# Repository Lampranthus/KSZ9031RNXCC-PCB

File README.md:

# Spartan-6 1GbE Interface

A **1 Gbps Ethernet UDP communication system** implemented on a Xilinx Spartan-6 FPGA with a KSZ9031 Gigabit PHY. Achieves ~1 Gbps throughput in TX, RX, and full-duplex modes, controlled via UART or UDP commands.

## Hardware

| Component | Part |
|-----------|------|
| FPGA | Xilinx Spartan-6 XC6SLX9-2TQG144C |
| PHY | KSZ9031RNXCC |
| Connector | ARJM11B1-502-AB-EW2 |

---

## Features

- **UDP TX/RX** at line rate (~1 Gbps)
- **Full-duplex** simultaneous TX + RX (237 MB/s measured)
- **UART control interface** — configure and trigger tests via serial commands
- **UDP command interface** — remotely set packet count, size, and rate
- **ARP support** — FPGA responds to ARP requests
- **Software shutdown mode** — low-power state via command (~159 mA)

---

## Board Controls

### Switches & LEDs

| Switch | Function | LED | Indicates |
|--------|----------|-----|-----------|
| SW[0] | Indicator state | LED[0] | Global reset_n |
| SW[1] | Indicator state | LED[1] | UART/MDIO reset_n |
| SW[2] | Indicator state | LED[2] | PHY PLL 125 MHz_n |
| SW[3] | Indicator state | LED[3] | PHY interrupt |
| SW[4] | Indicator state | LED[4] | UDP loopback mode |
| SW[5] | Indicator state | LED[5] | UDP random or constant data mode |
| SW[6] | Indicator state | LED[6] | UDP transmitting |
| SW[7] | Indicator state | LED[7] | MDIO busy |

### Push Buttons

| Button | Function |
|--------|----------|
| PUSH[0] | PHY reset |
| PUSH[1] | Reset UART and MDIO interfaces |
| PUSH[2] | Global reset |

---

## UDP Operation Modes

| Mode | Description |
|------|-------------|
| Default | Generate and transmit sequence data |
| Loopback | Echo received packets back to sender |
| Random data | Generate and transmit random data |
| Constant data | Transmit predefined data "X" or h58 |

---

## UART Command Interface

### Serial Configuration

| Parameter | Value |
|-----------|-------|
| Baud rate | 115200 |
| Data bits | 8 |
| Stop bits | 1 |
| Parity | None |

### Sending Commands

Commands are sent using `send_uart.py`. Multiple commands can be chained in a single call — they are concatenated in order with no separator:

```bash
python3 send_uart.py command1 command2 command3
```

> **Hardware constraint:** every transmission must be exactly **8 bytes or a multiple of 8 bytes**. The script enforces this and will error before touching the serial port if the length is wrong.

---

### UDP Control Commands
| Command | Hex | Description |
|---------|-----|-------------|
| `loopback` | `6C6F6F706261636B` | Enable loopback mode (LED[4] on) |
| `.trigger` | `2E74726967676572` | Send a trigger pulse |
| `..random` | `2E2E72616E646F6D` | Enable random data mode (LED[5] on) |
| `...flood` | `2E2E2E666C6F6F64` | Transmit as fast as possible |
| `udpmtu\xHH\xHH` | `7564706D7475HHHH` | Set MTU size (16-bit, default `\x05\xA0` = 1440 B) |
| `pktn\xHH\xHH\x00\x00` | `706B746EHHHHHHHH` | Set packet count per trigger (32-bit, default `\x00\x00\x00\x01` = 1) |

---

### IP / Network Configuration Commands
| Command | Hex | Description |
|---------|-----|-------------|
| `ip_g\xII\xII\xII\xII` | `69705F67IIIIIIII` | Set gateway IP (32-bit) |
| `ip_s\xII\xII\xII\xII` | `69705F73IIIIIIII` | Set local/source IP (32-bit) |
| `ip_d\xII\xII\xII\xII` | `69705F64IIIIIIII` | Set destination IP (32-bit) |
| `subm\xMM\xMM\xMM\xMM` | `7375626DMMMMMMM` | Set subnet mask (32-bit) |
| `srport\xPP\xPP` | `7372706F7274PPPP` | Set UDP source port (16-bit) |
| `dsport\xPP\xPP` | `6473706F7274PPPP` | Set UDP destination port (16-bit) |

> **IP format:** IPs are sent as raw 32-bit big-endian values.
> Example: `192.168.1.100` → `\xC0\xA8\x01\x64`

---

### MDIO / PHY Control Commands
| Command | Hex | Description |
|---------|-----|-------------|
| `..mdio_w` | `2E2E6D64696F5F77` | Switch to MDIO write mode |
| `..mdio_r` | `2E2E6D64696F5F72` | Switch to MDIO read mode (default) |
| `phyaddr\xHH` | `70687961646472HH` | Set PHY address (5 LSBs of `\xHH`, default `\x07`) |
| `regaddr\xHH` | `72656761646472HH` | Set register address (5 LSBs of `\xHH`, default `\x00`) |
| `mdio_d\xHH\xHH` | `6D64696F5F64HHHH` | Set 16-bit write data |
| `mdio_sta` | `6D64696F5F737461` | Start MDIO operation |

### MDIO Transaction Sequence

```
1. Set mode      →  ..mdio_r  or  ..mdio_w
2. Set PHY addr  →  phyaddr\xHH
3. Set reg addr  →  regaddr\xHH
4. Set data      →  mdio_d\xHH\xHH   (write operations only)
5. Execute       →  mdio_sta
```

Always return to read mode after a write to leave the interface in a safe state.

---

## Command Examples

### Read PHY register (default config)

```bash
python3 send_uart.py ..mdio_r "phyaddr\x07" "regaddr\x00" mdio_sta
```

Sequence: read mode → PHY 7 → register 0 → execute

---

### Write to PHY register, then read back to confirm

```bash
python3 send_uart.py ..mdio_w "phyaddr\x07" "regaddr\x00" "mdio_d\x11\x40" mdio_sta ..mdio_r mdio_sta
```

| Step | Command | Action |
|------|---------|--------|
| 1 | `..mdio_w` | Switch to write mode |
| 2 | `phyaddr\x07` | Target PHY 7 |
| 3 | `regaddr\x00` | Target register 0 |
| 4 | `mdio_d\x11\x40` | Write data = 0x1140 |
| 5 | `mdio_sta` | Execute write |
| 6 | `..mdio_r` | Switch back to read mode |
| 7 | `mdio_sta` | Execute read (verify) |

---

### Common MDIO sequences

| Purpose | Command |
|---------|---------|
| Read PHY 7, reg 0 | `python3 send_uart.py ..mdio_r "phyaddr\x07" "regaddr\x00" mdio_sta` |
| Write default config (PHY 7, reg 0) | `python3 send_uart.py ..mdio_w "phyaddr\x07" "regaddr\x00" "mdio_d\x11\x40" mdio_sta ..mdio_r mdio_sta` |
| Software reset (PHY 7) | `python3 send_uart.py ..mdio_w "phyaddr\x07" "regaddr\x00" "mdio_d\x91\x40" mdio_sta ..mdio_r mdio_sta` |
| Power down (PHY 7) | `python3 send_uart.py ..mdio_w "phyaddr\x07" "regaddr\x00" "mdio_d\x19\x40" mdio_sta ..mdio_r mdio_sta` |

---

### MDIO MMD Register Access

MMD (MIIM Managed Device) registers are accessed indirectly using the **MDIO address registers D (0x0D) and E (0x0E)**.

The access sequence is always:
1. Write the MMD device address to register `0x0D`
2. Write the target register address to register `0x0E`
3. Write the function (read/write + optional auto-increment) back to `0x0D`
4. Read or write data via register `0x0E`

#### Write MMD — Example: MMD device `0x02`, register `0x00` ← `0x0010`

```bash
# Step 1 — Select MMD device address (device = 0x02)
python3 send_uart.py ..mdio_w "phyaddr\x07" "regaddr\x0D" "mdio_d\x00\x02" mdio_sta

# Step 2 — Select target register inside the MMD (register = 0x0000)
python3 send_uart.py ..mdio_w "phyaddr\x07" "regaddr\x0E" "mdio_d\x00\x00" mdio_sta

# Step 3 — Switch to data function, no auto-increment (0x4000 | device)
python3 send_uart.py ..mdio_w "phyaddr\x07" "regaddr\x0D" "mdio_d\x40\x02" mdio_sta

# Step 4 — Write new data to the MMD register
python3 send_uart.py ..mdio_w "phyaddr\x07" "regaddr\x0E" "mdio_d\x00\x10" mdio_sta
```

> **`0x4002`** = data function (bits [15:14] = `01`) + device `0x02`, no auto-increment.
> **`0x8002`** = data function with post-increment (bits [15:14] = `10`) + device `0x02`.

---

#### Read MMD — Example: MMD device `0x02`, registers `0x00` → `0x02` (burst with auto-increment)

```bash
# Step 1 — Select MMD device address (device = 0x02)
python3 send_uart.py ..mdio_w "phyaddr\x07" "regaddr\x0D" "mdio_d\x00\x02" mdio_sta

# Step 2 — Select starting register (register = 0x0000)
python3 send_uart.py ..mdio_w "phyaddr\x07" "regaddr\x0E" "mdio_d\x00\x00" mdio_sta

# Step 3 — Switch to data function WITH auto-increment (0x8000 | device)
python3 send_uart.py ..mdio_w "phyaddr\x07" "regaddr\x0D" "mdio_d\x80\x02" mdio_sta

# Step 4 — Read register 0x00
python3 send_uart.py ..mdio_r "phyaddr\x07" "regaddr\x0E" mdio_sta

# Step 5 — Read register 0x01 (auto-incremented)
python3 send_uart.py ..mdio_r "phyaddr\x07" "regaddr\x0E" mdio_sta

# Step 6 — Read register 0x02 (auto-incremented)
python3 send_uart.py ..mdio_r "phyaddr\x07" "regaddr\x0E" mdio_sta
```

---

#### One-liner shortcuts

```bash
# Full write — MMD 0x02, reg 0x00 ← 0x0008
python3 send_uart.py ..mdio_w \
  "phyaddr\x07" "regaddr\x0D" "mdio_d\x00\x02" mdio_sta \
  "regaddr\x0E" "mdio_d\x00\x00"               mdio_sta \
  "regaddr\x0D" "mdio_d\x40\x02"               mdio_sta \
  "regaddr\x0E" "mdio_d\x00\x08"               mdio_sta

# Full read — MMD 0x02, reg 0x00 (single, no auto-increment)
python3 send_uart.py ..mdio_w \
  "phyaddr\x07" "regaddr\x0D" "mdio_d\x00\x02" mdio_sta \
  "regaddr\x0E" "mdio_d\x00\x00"               mdio_sta \
  "regaddr\x0D" "mdio_d\x40\x02"               mdio_sta \
  ..mdio_r "regaddr\x0E" mdio_sta
```

#### Register `0x0D` function field reference

| Bits [15:14] | Value | Function |
|---|---|---|
| `00` | `0x0000` \| device | Address function — points to MMD register |
| `01` | `0x4000` \| device | Data function — no auto-increment |
| `10` | `0x8000` \| device | Data function — post-increment on each access read or write |
| `11` | `0xC000` \| device | Data function — post increment on writes only |

---

## Network Setup

Set up a `192.168.1.1/24` network between your PC and the FPGA:

| Device | IP Address |
|--------|------------|
| FPGA (default) | `192.168.1.12` |
| PC (default) | `192.168.1.11` |

> IPv6 must be disabled on the interface for compatibility.

Configure the PC interface:

```bash
sudo ip addr flush dev eth0
sudo ip addr add 192.168.1.11/24 dev eth0
sudo ip link set eth0 up
```

Verify ARP (confirms the FPGA link is up):

```bash
sudo arping -I eth0 -c 10 192.168.1.12
```

---

## Throughput Tests

### TX Test (~1 Gbps)

Terminal 1 — monitor traffic:
```bash
sudo tcpdump -i eth0 udp -w - | pv > /dev/null
```

Terminal 2 — trigger transmission (set ~1 M packets first for accurate results):
```bash
python3 send_uart.py .trigger
```

> Expected: **~118 MB/s ≈ 0.994 Gbps**

---

### RX Test

Terminal 1 — flood UDP packets to the FPGA:
```bash
sudo hping3 192.168.1.12 -2 -p 1234 -d 1440 --flood
```

Terminal 2 — monitor received traffic:
```bash
sudo tcpdump -i eth0 udp -w - | pv > /dev/null
```

---

### Full-Duplex Test (TX + RX simultaneously)

Run both the TX and RX tests at the same time and monitor with:
```bash
sudo tcpdump -i eth0 udp -w - | pv > /dev/null
```

> **Measured: 237 MB/s (~1 Gbps full-duplex confirmed)**
> ```
> tcpdump: listening on eth0, link-type EN10MB (Ethernet), snapshot length 262144 bytes
> 26.9GiB 0:03:54 [236MiB/s]
> ```

---

## Power Consumption

Measurements include FPGA + PHY at 1 Gbps link speed.

| Mode | Current |
|------|---------|
| Standby (1 Gbps link up) | ~467 mA |
| Software shutdown | ~159 mA |
| Full duplex (1 Gbps) | ~552 mA |

---

## Troubleshooting

| Symptom | Solution |
|---------|---------|
| No response from FPGA | Check USB connection and power supply |
| LEDs all off | Verify switch positions (SW[1] enables LEDs) |
| LED[7] stuck on | MDIO busy — wait for operation to complete before sending next command |
| Unexpected data received | Verify baud rate is set to 115200 |
| Script errors before sending | Payload length must be a multiple of 8 bytes — add `\x00` padding |

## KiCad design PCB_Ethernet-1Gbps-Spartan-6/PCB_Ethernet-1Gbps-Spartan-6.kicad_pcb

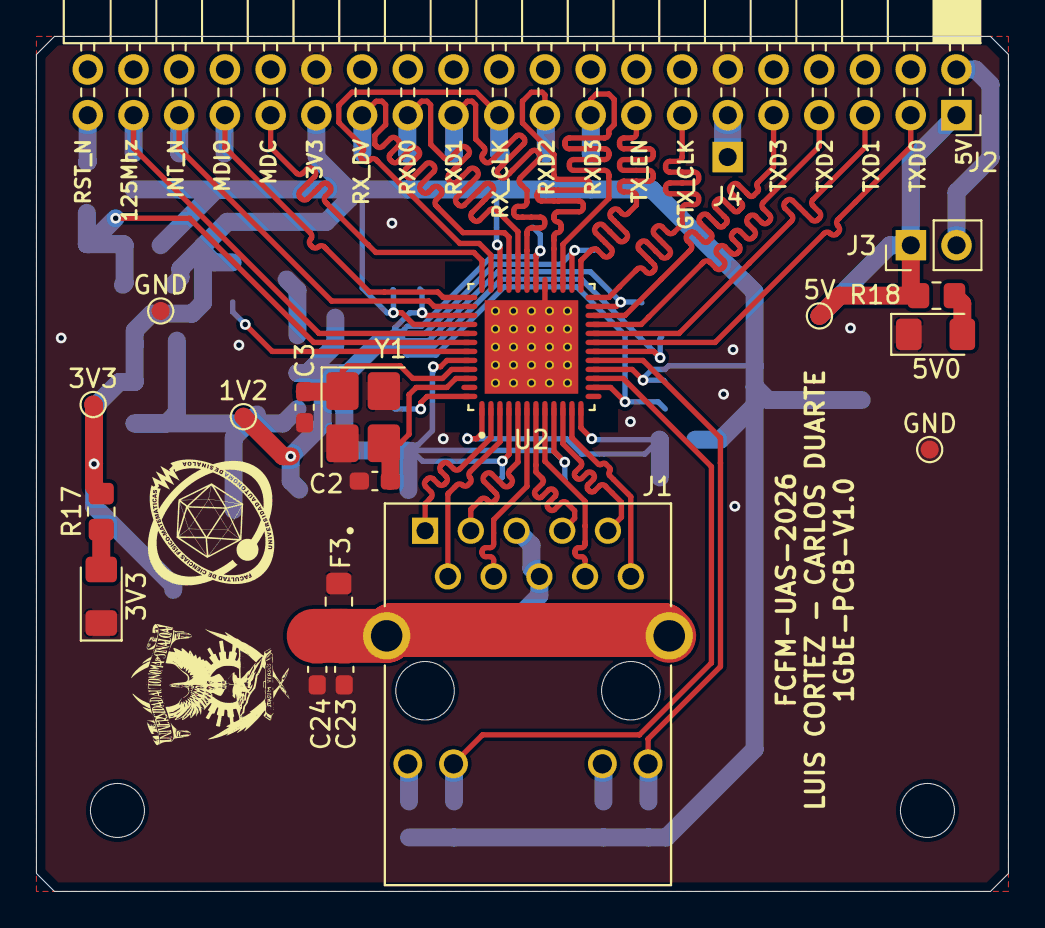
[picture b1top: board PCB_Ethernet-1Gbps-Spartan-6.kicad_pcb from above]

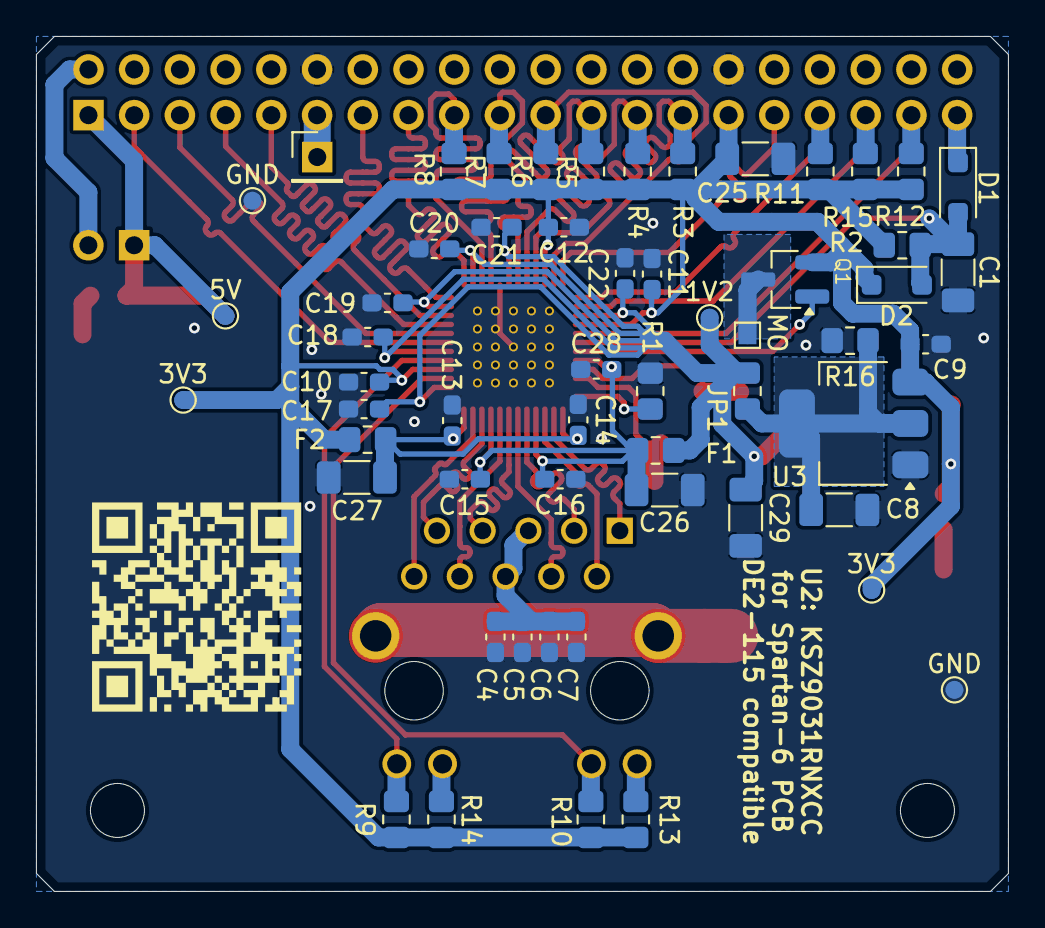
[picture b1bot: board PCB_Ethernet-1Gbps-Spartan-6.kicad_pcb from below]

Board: 2 copper layers, 54.0 x 47.5 mm, 75 parts (56 on the bottom side), 48 nets.

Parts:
1V2, 1V2#2, 3V3#2, 3V3#3, 3V3#4, 5V, 5V#2: TestPoint_Pad_D1.0mm
3V3, 5V0: LED; LED_1206_3216Metric_Pad1.42x1.75mm_HandSolder
C1, C8, C25, C26, C27, C29: 10uF; C_1206_3216Metric_Pad1.33x1.80mm_HandSolder
C2, C3: 22pF; C_0603_1608Metric_Pad1.08x0.95mm_HandSolder
C4, C5, C6, C7, C9, C10, C11, C12, C13, C14, C15, C16, C17, C18, C19, C20, C21, C22, C23, C24, C28: 0.1uF; C_0603_1608Metric_Pad1.08x0.95mm_HandSolder
D1, D2: 1N4148; D_SOD-123F
F1, F2, F3: 0; R_0805_2012Metric_Pad1.20x1.40mm_HandSolder
GND: TestPoint_Pad_D1.0mm
GND#2, GND#3, GND#4: TestPoint_Pad_D1.0mm
J1: ARJM11B1-502-AB-EW2; ABRACON_ARJM11B1-502-AB-EW2
J2: Conn_02x20_Odd_Even; PinSocket_2x20_P2.54mm_Horizontal
J3: Conn_01x02_Pin; PinHeader_1x02_P2.54mm_Vertical
J4: Conn_01x01_Pin; PinHeader_1x01_P2.54mm_Vertical
JP1: 0; R_0805_2012Metric_Pad1.20x1.40mm_HandSolder
MO: TestPoint_Pad_1.0x1.0mm
Q1: PMOS; SOT-23_Handsoldering
R1: 12.1k; R_0805_2012Metric_Pad1.20x1.40mm_HandSolder
R2, R3, R4, R5, R6, R7, R8, R9, R10, R12: 10k; R_0805_2012Metric_Pad1.20x1.40mm_HandSolder
R11, R15: 1k; R_0805_2012Metric_Pad1.20x1.40mm_HandSolder
R13, R14, R17, R18: 220; R_0805_2012Metric_Pad1.20x1.40mm_HandSolder
R16: 120; R_0805_2012Metric_Pad1.20x1.40mm_HandSolder
U2: KSZ9031RNXCC; IC_KSZ9031RNXCC
U3: LD1117S12TR_SOT223; SOT-223-3_TabPin2
Y1: 25Mhz; Crystal_SMD_3225-4Pin_3.2x2.5mm_HandSoldering

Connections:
1.2V: 1V2.1, 1V2#2.1, C17.2, C18.2, C19.2, C20.2, C21.2, C22.2, C29.1, F1.2, JP1.1, U2.14 (DVDDL), U2.18 (DVDDL__1), U2.23 (DVDDL__2), U2.26 (DVDDL__3), U2.30 (DVDDL__4), U2.39 (DVDDL__5)
1V2_L: C8.1, JP1.2, R16.2, U3.2 (VO)
3.3V: 3V3#2.1, 3V3#3.1, 3V3#4.1, C9.2, C10.2, C11.2, C12.2, C25.1, D2.1 (K), F2.2, J2.29, Q1.3 (S), R2.2, R3.2, R4.2, R5.2, R6.2, R7.2, R8.2, R9.2, R10.2, R11.2, R12.2, R13.2, R14.2, R15.2, R17.2, U2.16 (DVDDH), U2.34 (DVDDH__1), U2.40 (DVDDH__2), U3.3 (VI)
5V: 5V.1, 5V#2.1, J2.1, J3.1, R18.2
125Mhz: J2.37, R12.1, U2.41 (CLK125_NDO/LED_MODE)
A1.2V: C15.2, C16.2, C26.1, C28.2, F1.1, U2.4 (AVDDL), U2.9 (AVDDL__1), U2.44 (AVDDL_PLL)
A3.3V: C13.2, C14.2, C27.1, F2.1, U2.1 (AVDDH), U2.12 (AVDDH__1)
AGND: C23.2, C24.2, F3.2, J1.S1 (SHIELD), J1.S2 (SHIELD__1)
CT: C4.2, C5.2, C6.2, C7.2, J1.5 (CT), J1.6 (CT__1)
GND: 3V3.1 (K), 5V0.1 (K), C1.2, C2.2, C3.2, C4.1, C5.1, C6.1, C7.1, C8.2, C9.1, C10.1, C11.1, C12.1, C13.1, C14.1, C15.1, C16.1, C17.1, C18.1, C19.1, C20.1, C21.1, C22.1, C23.1, C24.1, C25.2, C26.2, C27.2, C28.1, C29.2, F3.1, GND.1, GND#2.1, GND#3.1, GND#4.1, J2.12, J2.30, R1.1, R16.1, U2.29 (VSS), U2.49 (P_GND), U2.49_1 (P_GND__1), U2.49_2 (P_GND__2), U2.49_3 (P_GND__3), U2.49_4 (P_GND__4), U2.49_5 (P_GND__5), U2.49_6 (P_GND__6), U2.49_7 (P_GND__7), U2.49_8 (P_GND__8), U2.49_9 (P_GND__9), U2.49_10 (P_GND__10), U2.49_11 (P_GND__11), U2.49_12 (P_GND__12), U2.49_13 (P_GND__13), U2.49_14 (P_GND__14), U2.49_15 (P_GND__15), U2.49_16 (P_GND__16), U2.49_17 (P_GND__17), U2.49_18 (P_GND__18), U2.49_19 (P_GND__19), U2.49_20 (P_GND__20), U2.49_21 (P_GND__21), U2.49_22 (P_GND__22), U2.49_23 (P_GND__23), U2.49_24 (P_GND__24), U2.49_25 (P_GND__25), U3.1 (GND), Y1.2, Y1.4
GTX_CLK: J2.13, U2.24 (GTX_CLK)
INT_N: J2.35, R15.1, U2.38 (INT_N/PME_N2)
LDO_1V2: MO.1, Q1.1 (D)
LDO_O: Q1.2 (G), U2.43 (LDO_O)
LED1: J1.14, R9.1, U2.17 (LED1/PHYAD0/PME_N1)
LED2: J1.12, R10.1, U2.15 (LED2/PHYAD1)
MDC: J2.31, U2.36 (MDC)
MDIO: J2.33, R11.1, U2.37 (MDIO)
unnamed: 3V3.2 (A), R17.1
unnamed: 5V0.2 (A), R18.1
unnamed: C1.1, D1.2 (A), D2.2 (A), R2.1, U2.42 (~RESET_N)
unnamed: J1.11, R13.1
unnamed: J1.13, R14.1
unnamed: J2.2, J3.2
unnamed: J2.11, J4.1
unnamed: R1.2, U2.48 (ISET)
unnamed: C2.1, U2.46 (XI), Y1.3
unnamed: C3.1, U2.45 (XO), Y1.1
RST_N: D1.1 (K), J2.39
RXD0: J2.25, R5.1, U2.32 (RXD0/MODE0)
RXD1: J2.23, R6.1, U2.31 (RXD1/MODE1)
RXD2: J2.19, R7.1, U2.28 (RXD2/MODE2)
RXD3: J2.17, R8.1, U2.27 (RXD3/MODE3)
RX_CLK: J2.21, R3.1, U2.35 (RX_CLK/PHYAD2)
RX_DV: J2.27, R4.1, U2.33 (RX_DV/CLK125_EN)
TD1+: J1.1 (TD1+), U2.2 (TXRXP_A)
TD1-: J1.2 (TD1-), U2.3 (TXRXM_A)
TD2+: J1.3 (TD2+), U2.5 (TXRXP_B)
TD2-: J1.4 (TD2-), U2.6 (TXRXM_B)
TD3+: J1.7 (TD3+), U2.7 (TXRXP_C)
TD3-: J1.8 (TD3-), U2.8 (TXRXM_C)
TD4+: J1.9 (TD4+), U2.10 (TXRXP_D)
TD4-: J1.10 (TD4-), U2.11 (TXRXM_D)
TXD0: J2.3, U2.19 (TXD0)
TXD1: J2.5, U2.20 (TXD1)
TXD2: J2.7, U2.21 (TXD2)
TXD3: J2.9, U2.22 (TXD3)
TX_EN: J2.15, U2.25 (TX_EN)

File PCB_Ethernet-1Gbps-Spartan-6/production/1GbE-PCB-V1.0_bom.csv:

Designator,Footprint,Quantity,Value,LCSC Part #
"3V3_4, 5V1",1206,2,LED,
"C1, C25, C26, C27, C29, C8",1206,6,10uF,
"C10, C11, C12, C13, C14, C15, C16, C17, C18, C19, C20, C21, C22, C23, C24, C28, C4, C5, C6, C7, C9",0603,21,0.1uF,
"C2, C3",0603,2,22pF,
"D1, D2",D_SOD-123F,2,1N4148,
"F1, F2, F3, JP1",0805,4,0,
J1,ABRACON_ARJM11B1-502-AB-EW2,1,ARJM11B1-502-AB-EW2,
J2,PinSocket_2x20_P2.54mm_Horizontal,1,Conn_02x20_Odd_Even,
J3,PinHeader_1x02_P2.54mm_Vertical,1,Conn_01x02_Pin,
Q1,SOT-23_Handsoldering,1,PMOS,
R1,0805,1,12.1k,
"R10, R12, R2, R3, R4, R5, R6, R7, R8, R9",0805,10,10k,
"R11, R15",0805,2,1k,
"R13, R14, R17, R18",0805,4,220,
R16,0805,1,120,
U2,IC_KSZ9031RNXCC,1,KSZ9031RNXCC,
U3,SOT-223-3_TabPin2,1,LD1117S12TR_SOT223,
Y1,Crystal_SMD_3225-4Pin_3.2x2.5mm_HandSoldering,1,25Mhz,

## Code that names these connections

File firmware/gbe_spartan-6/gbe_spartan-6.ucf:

NET "*" IOSTANDARD=LVCMOS33;
CONFIG VCCAUX = "2.5" ;

// 50Mhz Clock
NET "clk" LOC = "P56";
NET "clk" TNM_NET = "sys_clk_pin";
TIMESPEC "TS_sys_clk_pin" = PERIOD "sys_clk_pin" 20.000ns HIGH 50%;

// Dip Switch
NET "sw<0>" LOC = "P35";
NET "sw<1>" LOC = "P34";
NET "sw<2>" LOC = "P33";
NET "sw<3>" LOC = "P32";
NET "sw<4>" LOC = "P30";
NET "sw<5>" LOC = "P29";
NET "sw<6>" LOC = "P27";
NET "sw<7>" LOC = "P26";

// Red LEDs
NET "led<0>" LOC = "P74";
NET "led<1>" LOC = "P75";
NET "led<2>" LOC = "P78";
NET "led<3>" LOC = "P79";
NET "led<4>" LOC = "P80";
NET "led<5>" LOC = "P81";
NET "led<6>" LOC = "P82";
NET "led<7>" LOC = "P83";

// Push buttons
NET "push<0>" LOC = "P144";
NET "push<1>" LOC = "P143";
NET "push<2>" LOC = "P142";

// UART
NET "txd" LOC = "P100";
NET "rxd" LOC = "P101";

// Molex
//NET "molex<0>" LOC = "P141";
//NET "molex<1>" LOC = "P140";

// Single
//NET "pin0" LOC = "P139";

// Pin Header 
NET "ENET0_TX_DATA<0>" LOC = "P138" | SLEW = SLOW | DRIVE = 4; // RGMMII TXD0
NET "ENET0_TX_DATA<1>" LOC = "P137" | SLEW = SLOW | DRIVE = 4; // RGMMII TXD1
NET "ENET0_TX_DATA<2>" LOC = "P134" | SLEW = SLOW | DRIVE = 4; // RGMMII TXD2
NET "ENET0_TX_DATA<3>" LOC = "P133" | SLEW = SLOW | DRIVE = 4; // RGMMII TXD3
//NET "NC0" LOC = "P132"; // No connection
NET "ENET0_GTX_CLK" LOC = "P131" | SLEW = SLOW | DRIVE = 4; // RGMMII GTX_CLK
NET "ENET0_TX_EN" LOC = "P127" | SLEW = SLOW | DRIVE = 4; // RGMMII TX_EN
NET "ENET0_RX_DATA<3>" LOC = "P126" | IOB = TRUE; // RGMMII RXD3
NET "ENET0_RX_DATA<2>" LOC = "P124" | IOB = TRUE; // RGMMII RXD2 
NET "ENET0_RX_CLK" LOC = "P123" | IOB = TRUE; // RGMMII RX_CLK 
NET "ENET0_RX_CLK" TNM_NET = "rx_clk_pin";
TIMESPEC "TS_rx_clk_pin" = PERIOD "rx_clk_pin" 8.000ns HIGH 50%;
NET "ENET0_RX_DATA<1>" LOC = "P121" | IOB = TRUE; // RGMMII RXD1 
NET "ENET0_RX_DATA<0>" LOC = "P120" | IOB = TRUE; // RGMMII RXD0 
NET "ENET0_RX_DV" LOC = "P119" | IOB = TRUE; // RGMMII RX_DV
NET "V3_3" LOC = "P118"; // 3.3V in when pcb energized
NET "MDC" LOC = "P117";
NET "MDIO" LOC = "P116";
NET "ENET0_INT_N" LOC = "P115";
NET "CLK_125MHZ" LOC = "P114";
NET "ENET0_RST_N" LOC = "P112";  // RGMMII RST_N

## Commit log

2026-02-14 Kicad Added
2026-02-14 rev1
2026-02-17 rev2
2026-02-17 JLCV1
2026-02-19 rev3 firmware added
2026-03-23 mdio-and_uart_control_added
2026-03-23 Revise README for FPGA UDP Communication Controller
    Updated project name and added detailed documentation for hardware features, operation modes, UART communication protocol, and troubleshooting.
2026-03-25 Enhance README with Ethernet setup and UDP commands
    Added Ethernet configuration guide and UDP commands section to README.
2026-03-25 Update README with image and power consumption info
    Added image and power consumption details to README.
2026-03-25 Revise README for FPGA 1GbE Interface details
    Updated project title and enhanced overview with key features of the 1GbE UDP communication system.
2026-03-25 udp_control_added_tests_added
2026-03-28 Revise README for Spartan-6 1GbE Interface
    Updated README to reflect project details and features for Spartan-6 1GbE Interface.
2026-03-28 tested_version
2026-04-24 Update README with IP/Network Configuration commands
2026-04-25 flood_bug_fixed
2026-04-25 Document MDIO MMD register access procedures
    Added section on MDIO MMD register access with examples for read and write operations.
2026-05-07 Create technical document for Ethernet Gigabit testing
    Added a technical document outlining the standard Ethernet Gigabit testing procedures for FPGA, including hardware verification, link setup, transmission preparation, and standard test battery.
2026-05-07 Revise README for switches, UDP modes, and IP addresses
    Updated switch and LED descriptions, modified UDP operation modes, and corrected IP addresses in configuration commands.
2026-05-07 firmware_v1
2026-05-26 Add MIT License to the project
2026-05-26 udp_control_version
2026-05-28 Change static MAC address in notas.md
    Updated static MAC address for ARP configuration.
2026-05-28 Revise static MAC address configuration instructions
    Updated instructions for setting a static MAC address.
2026-06-24 sequence reset added
2026-06-24 sequence 16bit added
2026-06-24 sequence 16bit map ok added
